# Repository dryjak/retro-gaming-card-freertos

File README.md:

# 🎮 Interactive PCB Business Card & Pocket Console

## 📖 Overview
This project is a fully functional, credit-card-sized (53x85 mm) interactive business card that doubles as a minimalist handheld game console. Powered by an STM32 (prototype STM32F411RE, final version STM32C562KET) microcontroller and a LiPo battery, it was designed from scratch in KiCad to showcase complete hardware-software co-design. 

The goal of this project was to merge aesthetics with robust embedded engineering, tackling challenges such as mechanical constraints, power path optimization, and bare-metal/RTOS firmware development.

## ⚙️ Hardware Architecture
The board is designed with a focus on stability and signal integrity, featuring a sleek matte black soldermask and hidden testing interfaces.

* **Microcontroller:** STM32 series (prototype STM32F411RE, final version STM32C562KET), managing game logic and peripheral communication.
* **Display:** I2C OLED screen for high-contrast, low-power graphics.
* **Power Management:** Custom power path featuring a LiPo charging IC and a Low-Dropout Regulator (LDO) optimized for maximum battery life (minimizing voltage dropout).
* **PCB Layout Highlights:**
  * Mechanical collision avoidance (precise component placement avoiding mounting holes).
  * Concealed bottom-layer SWD Test Points (SWDIO, SWCLK, GND, 3.3V) to maintain a clean aesthetic on the front panel.

## 💻 Firmware & Software
The firmware is written in **C**, focusing on hardware abstraction and efficient resource management.
* Custom made liblaries for menu and games.
* (Optional for future) Power-saving modes to prevent LiPo over-discharge.
* (Optional for future) RTOS implementation for task scheduling (e.g., separating rendering tasks from button input polling).

The view of the PCB

Schematic
[Schematic.pdf](https://github.com/user-attachments/files/29943936/Schematic.pdf)

Layout
[Layout front.pdf](https://github.com/user-attachments/files/29943942/Layout.front.pdf)
[Lauout back.pdf](https://github.com/user-attachments/files/29943943/Lauout.back.pdf)

Basic schematic of STM32C562KET6

## 🗺️ System Block Diagram
```text
[ LiPo Battery ] --> [ Charger IC ] --> [ Low-Dropout (LDO) 3.3V ] 
                                                 |
                                                 v
[ User Buttons ] ------------------------> [ STM32 MCU ]
                                                 |
[ SWD Test Points ] <--------------------/       v
                                           [ OLED Display ]

```
Things to change:
1) Footprint 0.96 inch display - I used different pcb size - mistake
2) Add Rx and Tx pins for debugging
3) Change voltage devider placement, connection - connect it after on/off switch
4) Change footprint for battery connection

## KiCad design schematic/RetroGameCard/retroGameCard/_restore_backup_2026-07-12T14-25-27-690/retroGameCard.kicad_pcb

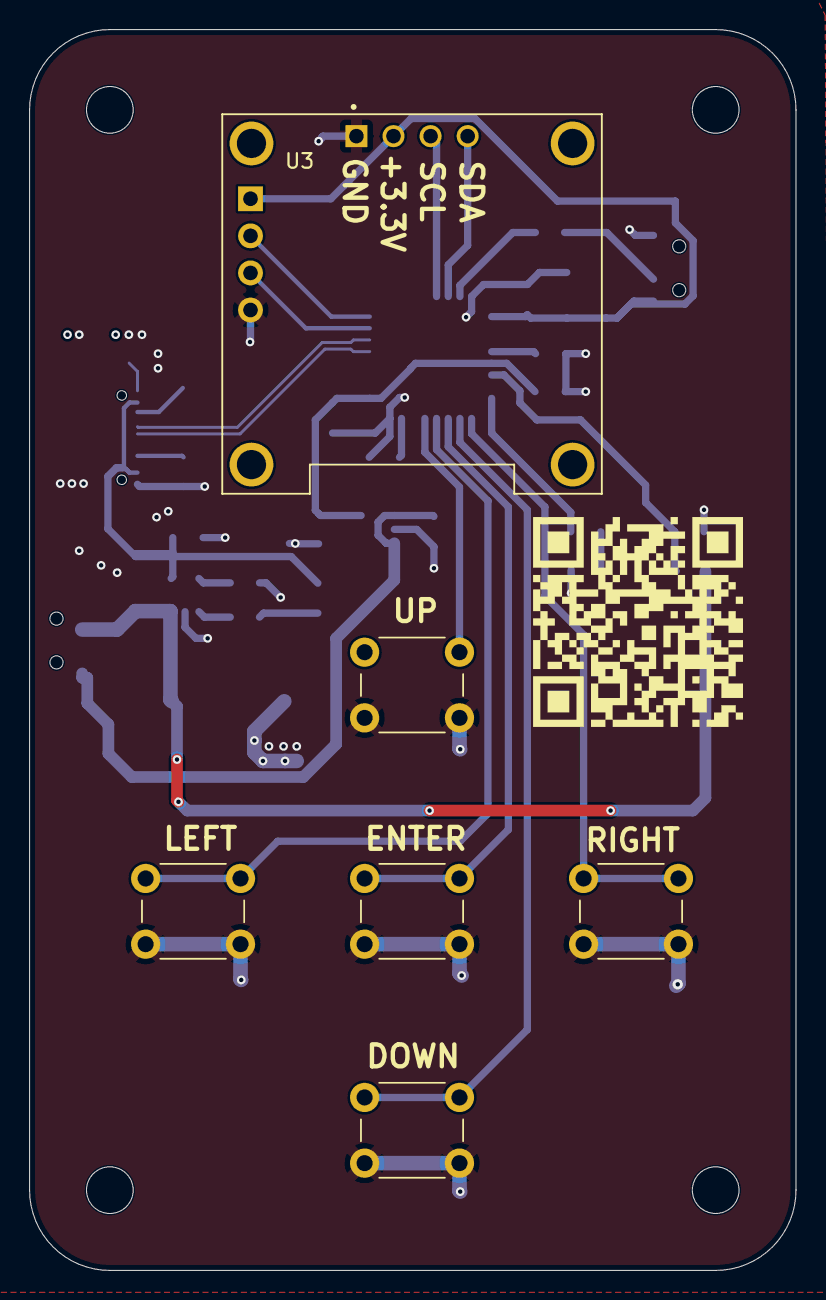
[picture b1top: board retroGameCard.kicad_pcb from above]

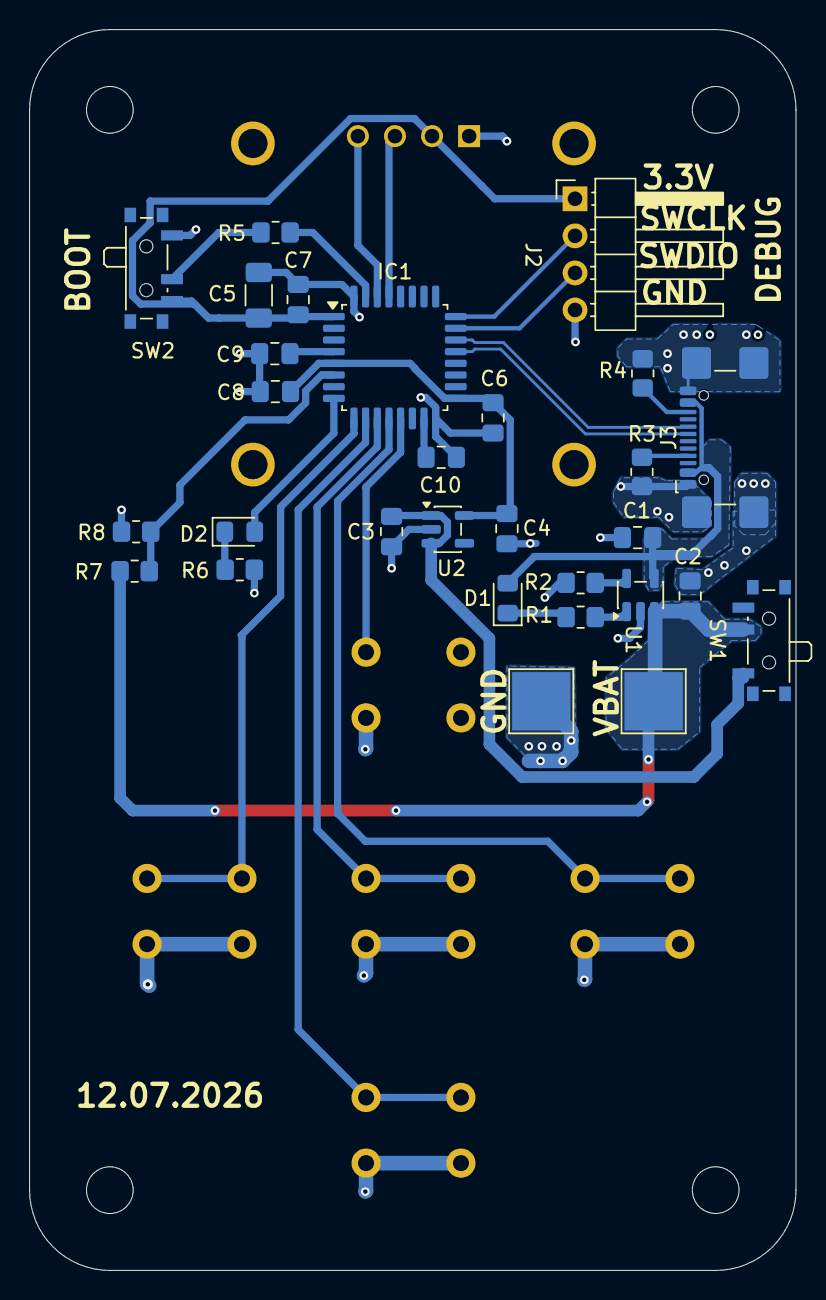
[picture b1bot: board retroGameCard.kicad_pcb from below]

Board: 2 copper layers, 52.5 x 85.0 mm, 38 parts (28 on the bottom side), 28 nets.

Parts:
C1, C2, C3, C4, C10: 4.7u; C_0805_2012Metric_Pad1.18x1.45mm_HandSolder
C5: 10u; C_1206_3216Metric_Pad1.33x1.80mm_HandSolder
C6, C7, C8, C9: 100n; C_0805_2012Metric_Pad1.18x1.45mm_HandSolder
C11: 1s lipo battery; Bez_nazwy_1
D1, D2: RED; LED_0805_2012Metric_Pad1.15x1.40mm_HandSolder
H1, H2, H3, H4: MountingHole; MountingHole_3.2mm_M3
IC1: STM32C562KET6; LQFP-32_7x7mm_P0.8mm
J2: Conn_01x04_Pin; PinHeader_1x04_P2.54mm_Horizontal
J3: USB_C_Receptacle_USB2.0_16P; USB_C_Receptacle_GCT_USB4110
R1: 470; R_0805_2012Metric_Pad1.20x1.40mm_HandSolder
R2, R6: 2k; R_0805_2012Metric_Pad1.20x1.40mm_HandSolder
R3, R4: 5.1k; R_0805_2012Metric_Pad1.20x1.40mm_HandSolder
R5: 10k; R_0805_2012Metric_Pad1.20x1.40mm_HandSolder
R7, R8: 100k; R_0805_2012Metric_Pad1.20x1.40mm_HandSolder
SW1: SW_Slide_DPDT; SW_SPDT_PCM12
SW2: SW_SPDT; SW_SPDT_PCM12
SW3, SW4, SW5, SW6, SW7: SW_Push; SW_PUSH_6mm
U1: MCP73831-2-OT; SOT-23-5
U2: AP2112K-3.3; SOT-23-5
U3: DM-OLED096-636; MODULE_DM-OLED096-636

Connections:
+3.3V: C4.1, C5.1, C6.1, C7.1, C8.1, IC1.1 (VDD_1), IC1.5 (VREF+), IC1.17 (VDD_2), J2.1, SW2.3 (C), U2.5 (VOUT), U3.2 (VCC_IN)
/ADC_VBATT: IC1.6 (PA0), R7.1, R8.2
/BOOT0: IC1.31 (PB8-BOOT0), R5.2
/DOWN: IC1.10 (PA4), SW4.1
/ENTER: IC1.11 (PA5), SW5.1
/LED: D2.2 (A), IC1.8 (PA2)
/LEFT: IC1.12 (PA6), SW3.1
/NRST: C9.1, IC1.4 (NRST)
/OLED_I2C_SCL: IC1.29 (PB6), U3.3 (SCL)
/OLED_I2C_SDA: IC1.30 (PB7), U3.4 (SDA)
/RIGHT: IC1.9 (PA3), SW7.1
/SWCLK: IC1.24 (PA14), J2.2
/SWDIO: IC1.23 (PA13), J2.3
/SW_BOOT: R5.1, SW2.2 (B)
/UP: IC1.13 (PA7), SW6.1
/USB_D+: IC1.22 (PA12), J3.A6 (D+), J3.B6 (D+)
/USB_D-: IC1.21 (PA11), J3.A7 (D-), J3.B7 (D-)
/Vbat: C2.1, C11.1, R7.2, SW1.2 (B), U1.3 (V_{BAT})
GND: C1.2, C2.2, C3.2, C4.2, C5.2, C6.2, C7.2, C8.2, C9.2, C10.2, C11.2, IC1.16 (VSS_1), IC1.32 (VSS_2), J2.4, J3.A1 (GND), J3.A12 (GND), J3.B1 (GND), J3.B12 (GND), J3.S1 (SHIELD), R2.1, R3.2, R4.1, R6.1, R8.1, SW2.1 (A), SW3.2, SW4.2, SW5.2, SW6.2, SW7.2, U1.2 (V_{SS}), U2.2 (GND), U3.1 (GND)
unnamed: D1.1 (K), R1.2
unnamed: D2.1 (K), R6.2
unnamed: C10.1, IC1.15 (VCAP)
unnamed: J3.A5 (CC1), R3.1
unnamed: J3.B5 (CC2), R4.2
unnamed: R2.2, U1.5 (PROG)
unnamed: R1.1, U1.1 (STAT)
unnamed: C3.1, SW1.1 (A), U2.1 (VIN), U2.3 (EN)
VBUS: C1.1, D1.2 (A), J3.A4 (VBUS), J3.A9 (VBUS), J3.B4 (VBUS), J3.B9 (VBUS), U1.4 (V_{DD})

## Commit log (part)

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2026-06-16 init function in oled lib
2026-06-16 Added Init function for oled ssd1306
2026-06-16 fixed bugs, initialization is working
2026-06-16 addedfunction to display data from buffer
2026-06-17 Added fuction to clear display
2026-06-17 added function to draw pixel
2026-06-17 added ghx files
2026-06-17 Oled liblary is working
2026-06-19 added button liblary to the project
2026-06-19 test button
2026-06-20 test buttons
2026-06-21 update on fsm came console
2026-06-22 update fmc liblary
2026-06-22 added function to draw menu
2026-06-22 added function to move up in menu
2026-06-22 added todo for tommorow tasks
2026-06-23 added all buttons
2026-06-23 fixed oled display
2026-06-23 added fonts liblary
2026-06-23 rotate oled
2026-06-23 added structures for moving in menu
2026-06-23 added to do for tommorow
2026-06-26 update settings section
2026-06-26 added left and right button
2026-06-26 buttons left and right are working
2026-06-26 fixed some bugs
2026-06-26 added min values for settings
2026-06-27 added function to change brightness
2026-06-28 added callback that changes brightness
2026-06-28 added callback play snake
2026-06-28 snake logic game liblary
2026-06-28 update turn on screen graphic
2026-06-28 changed description to eng
2026-06-28 changed graphic of dead screen
2026-06-29 added flappy bird liblary
2026-06-29 added flappy bird callbacks
2026-06-30 update bug in flppy bird game
2026-06-30 changed oled i2c to dma, changes functions in oled lib
2026-06-30 made symbol and footprint for STM32C562KET6
2026-06-30 added power rails
